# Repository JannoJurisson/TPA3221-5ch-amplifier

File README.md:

# TPA3221-5ch-amplifier
A D-class car amplifier based on TPA3221, replaces BOSE 294009 car amplifier PCB.

The amplifier uses a Push-pull SMPS with a SG3525 controller to boost 12V to 24V. Transformer is hand-made using non-gapped ferrite transformer core TDK E-50.
Similar E cores can be used as the transformer is fastened to the pcb using cable ties 

There a 5 channels:
Channel 1-4 -> speaker outputs (@ 4ohm speakers > ~4x60W)
Channel 5   -> subwoofer output (TPA3221 in PBTL operation, @ 4ohm woofer > ~100w)

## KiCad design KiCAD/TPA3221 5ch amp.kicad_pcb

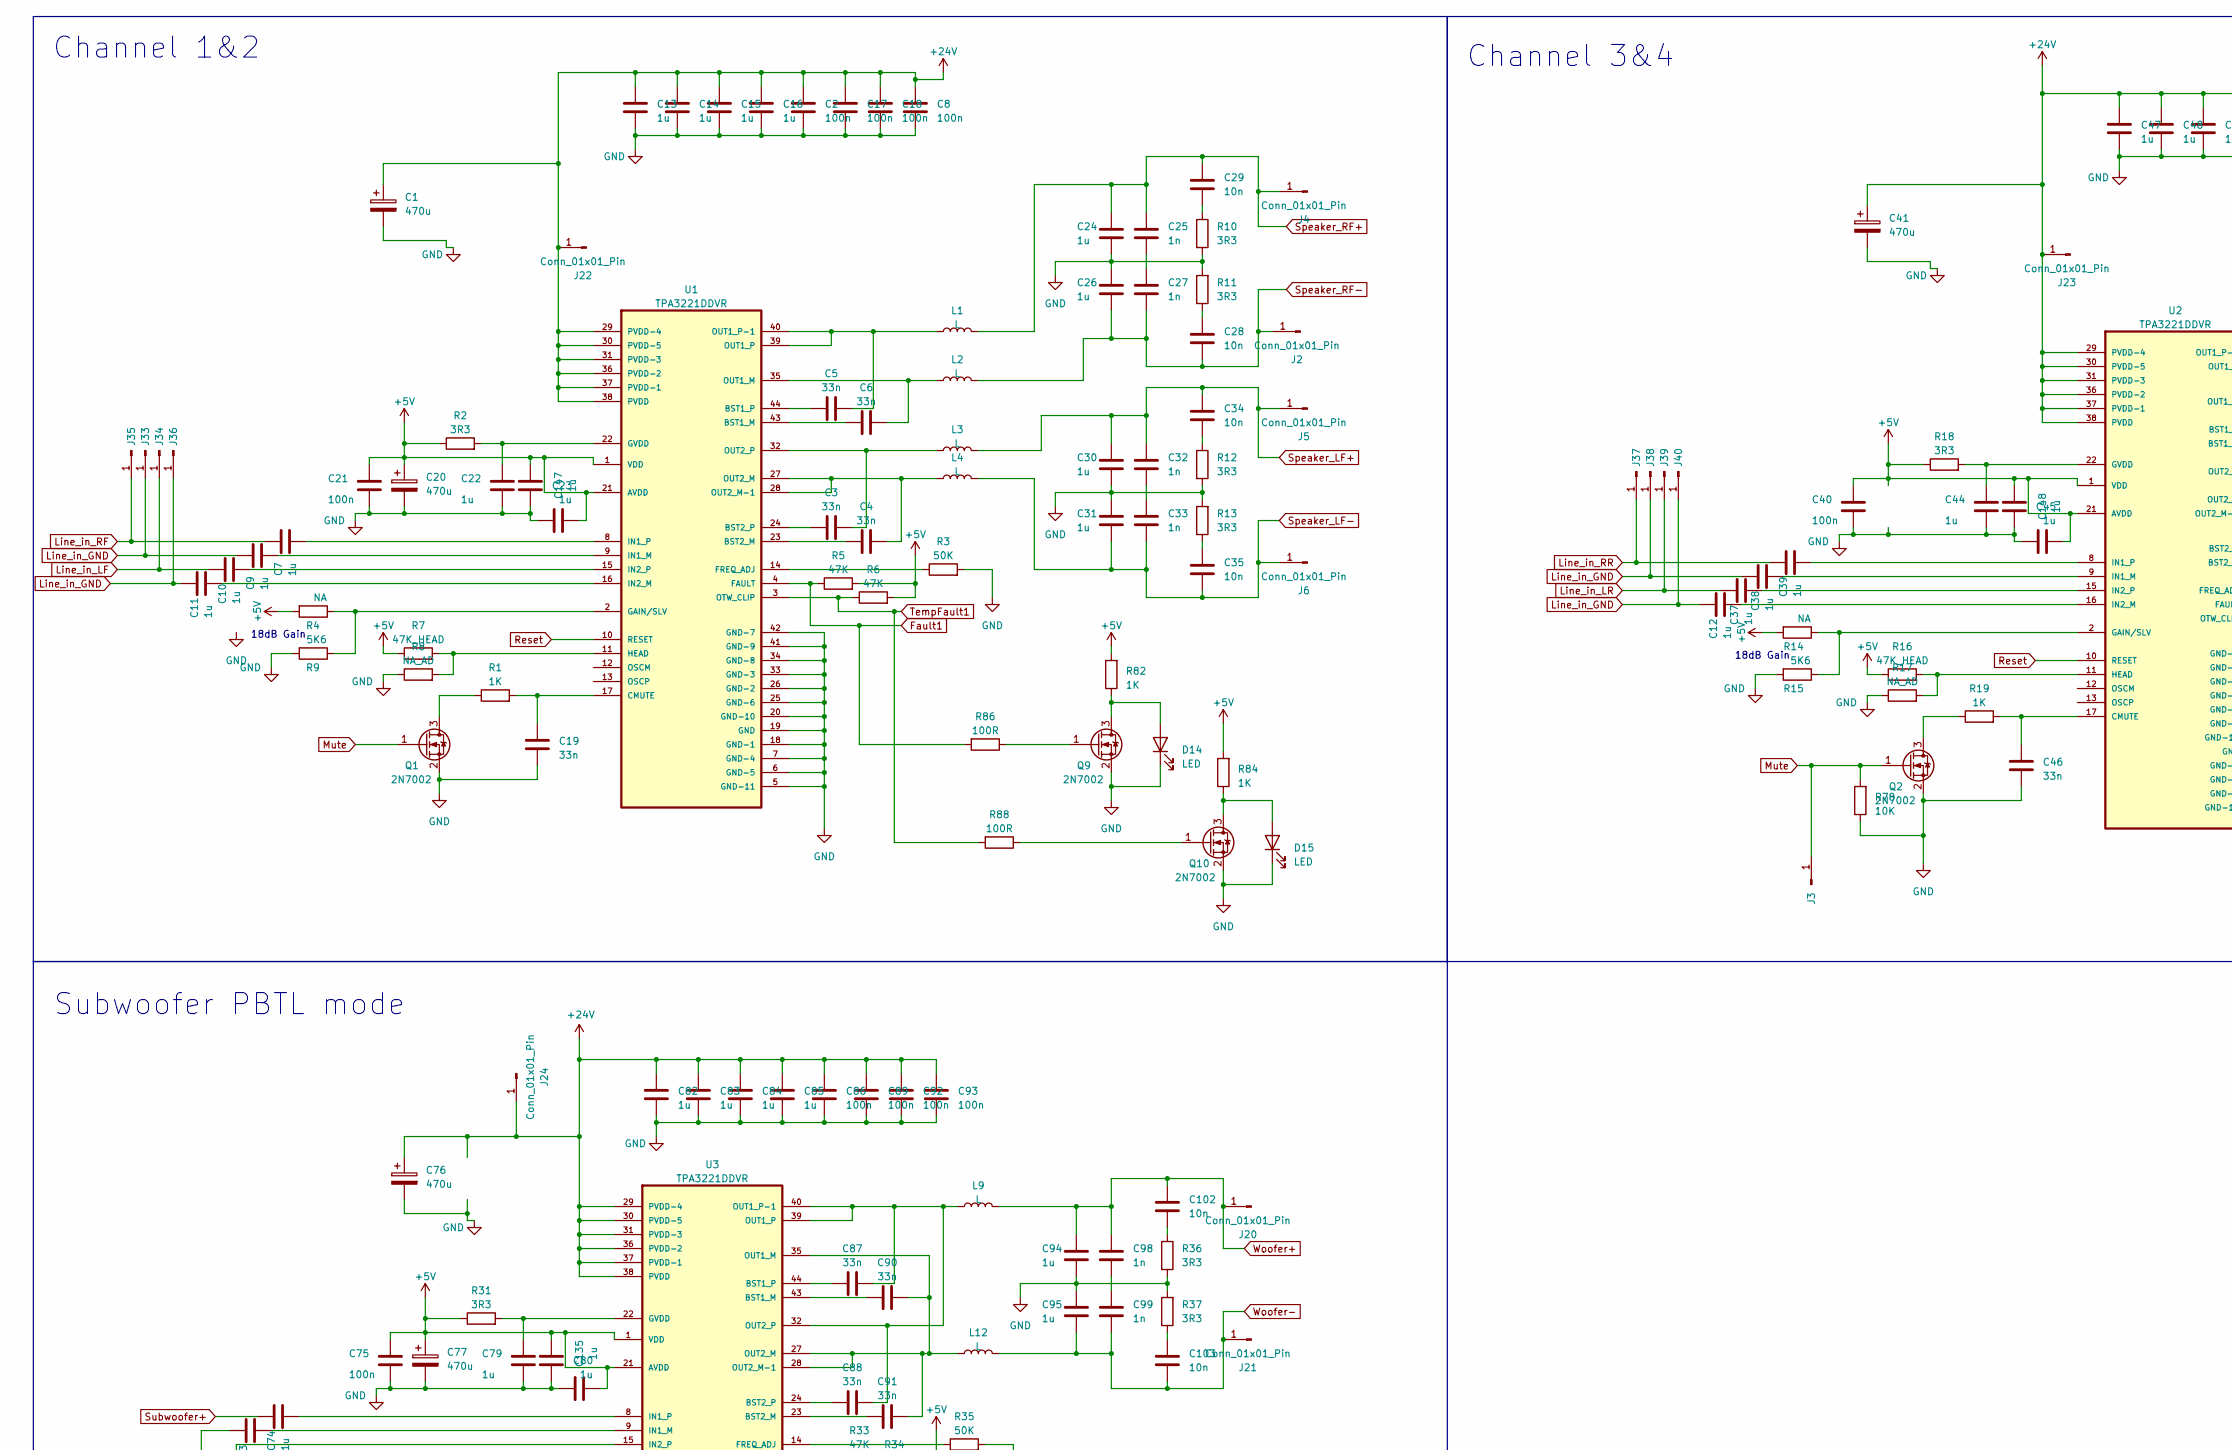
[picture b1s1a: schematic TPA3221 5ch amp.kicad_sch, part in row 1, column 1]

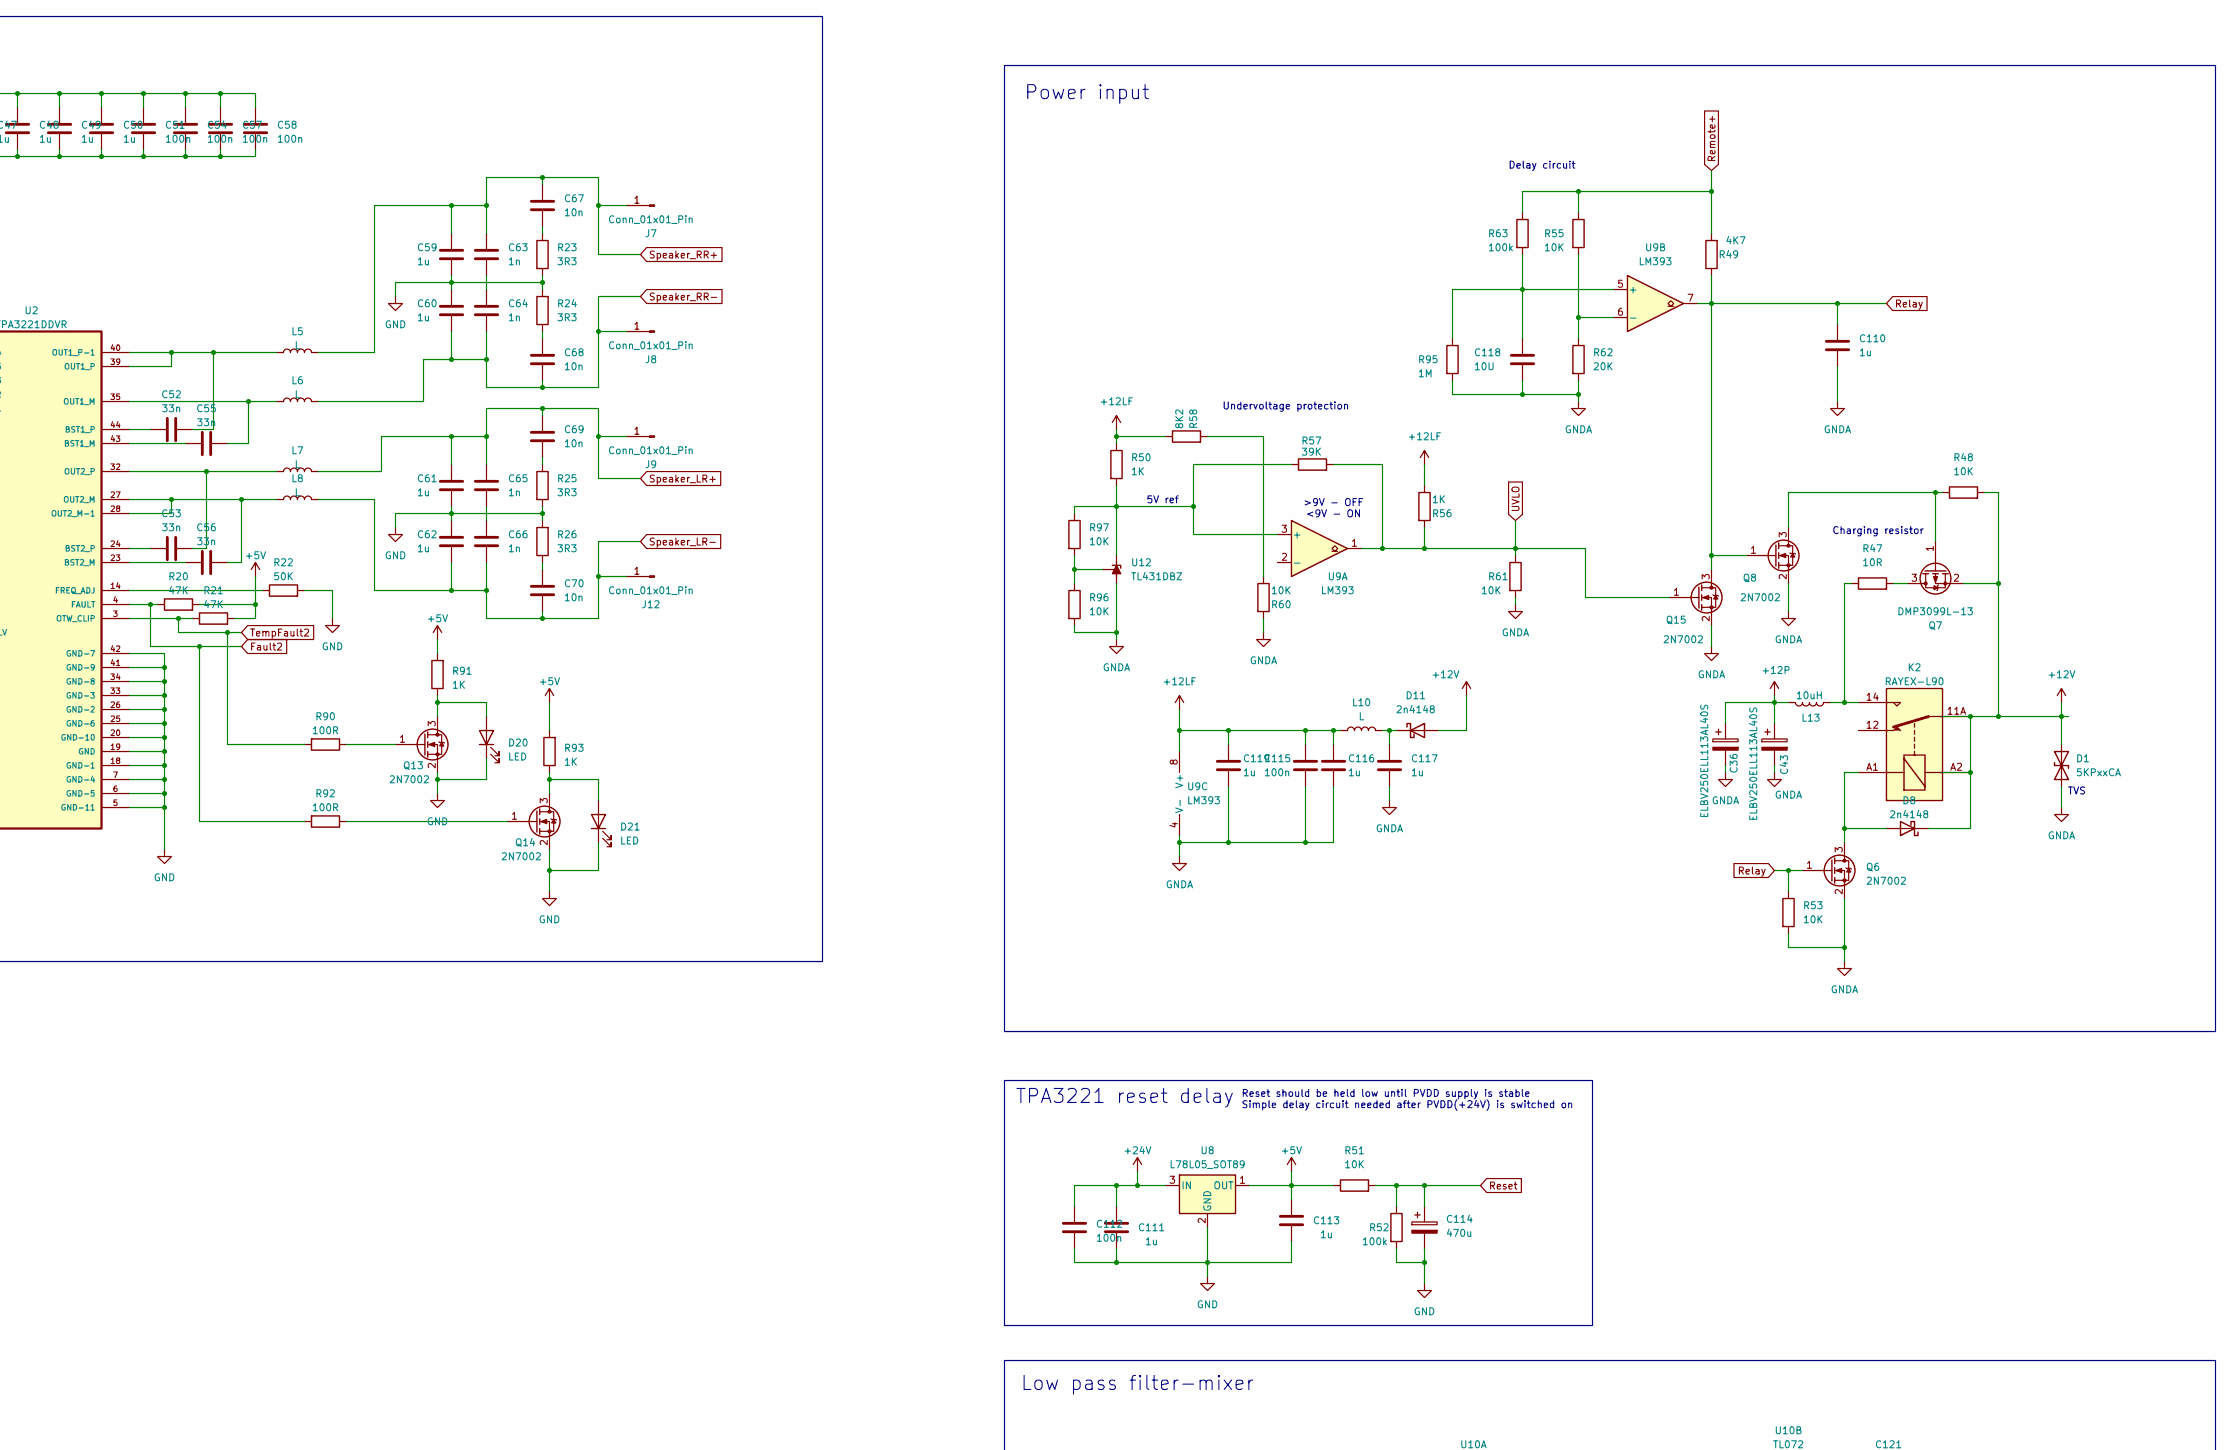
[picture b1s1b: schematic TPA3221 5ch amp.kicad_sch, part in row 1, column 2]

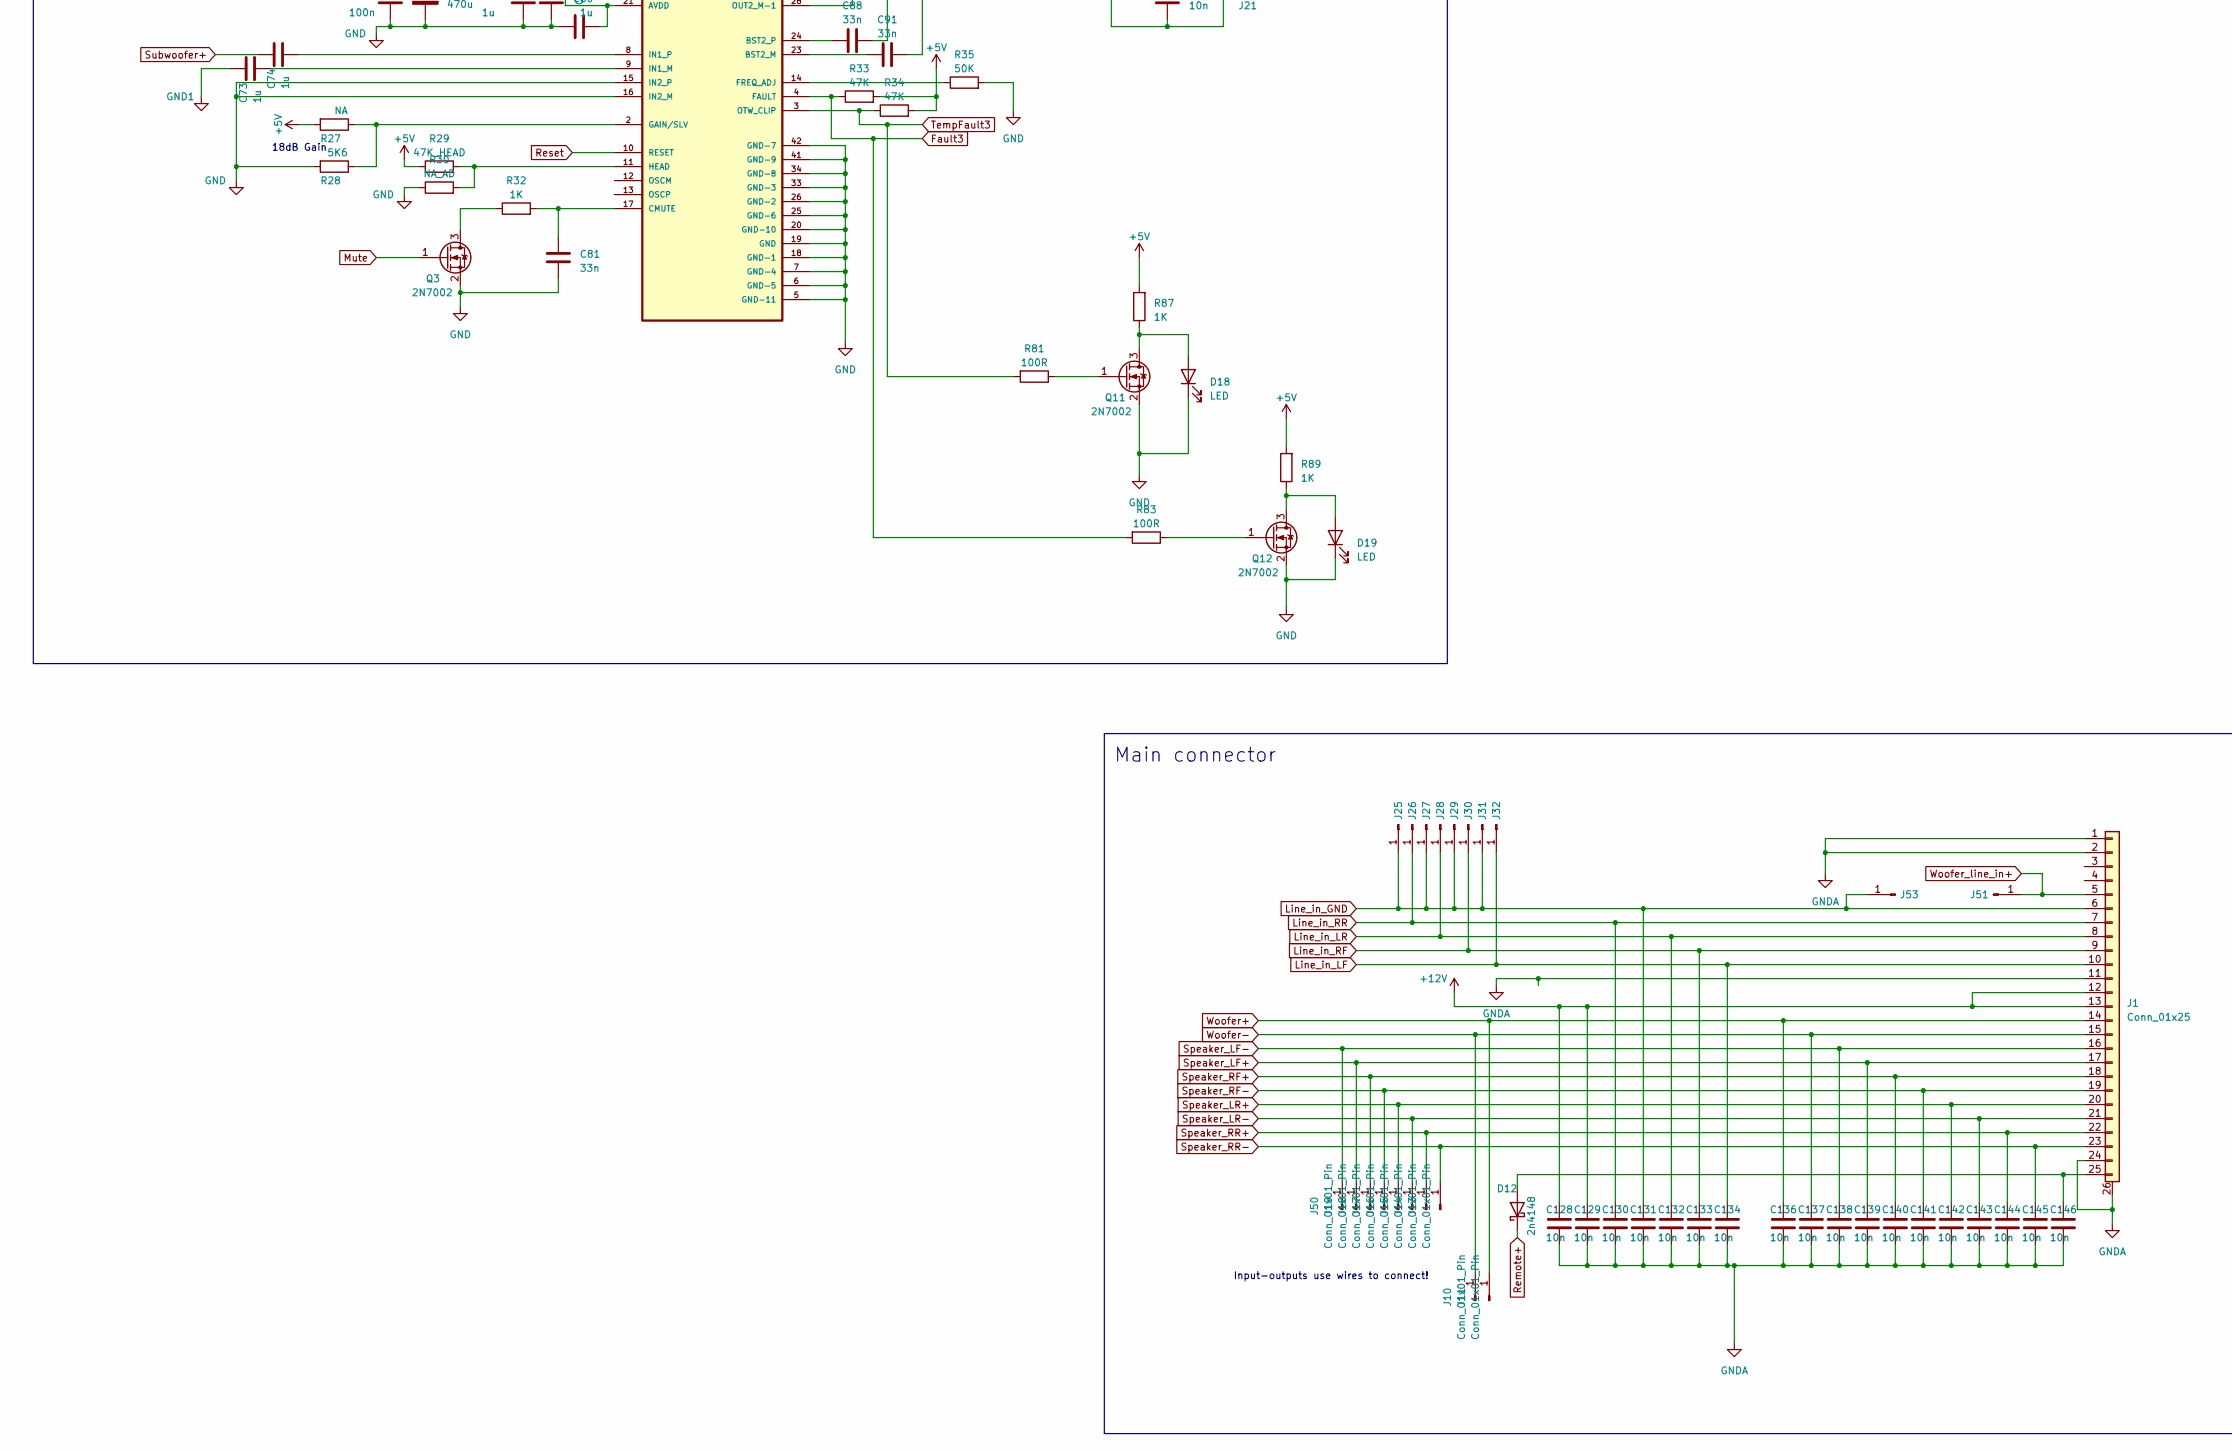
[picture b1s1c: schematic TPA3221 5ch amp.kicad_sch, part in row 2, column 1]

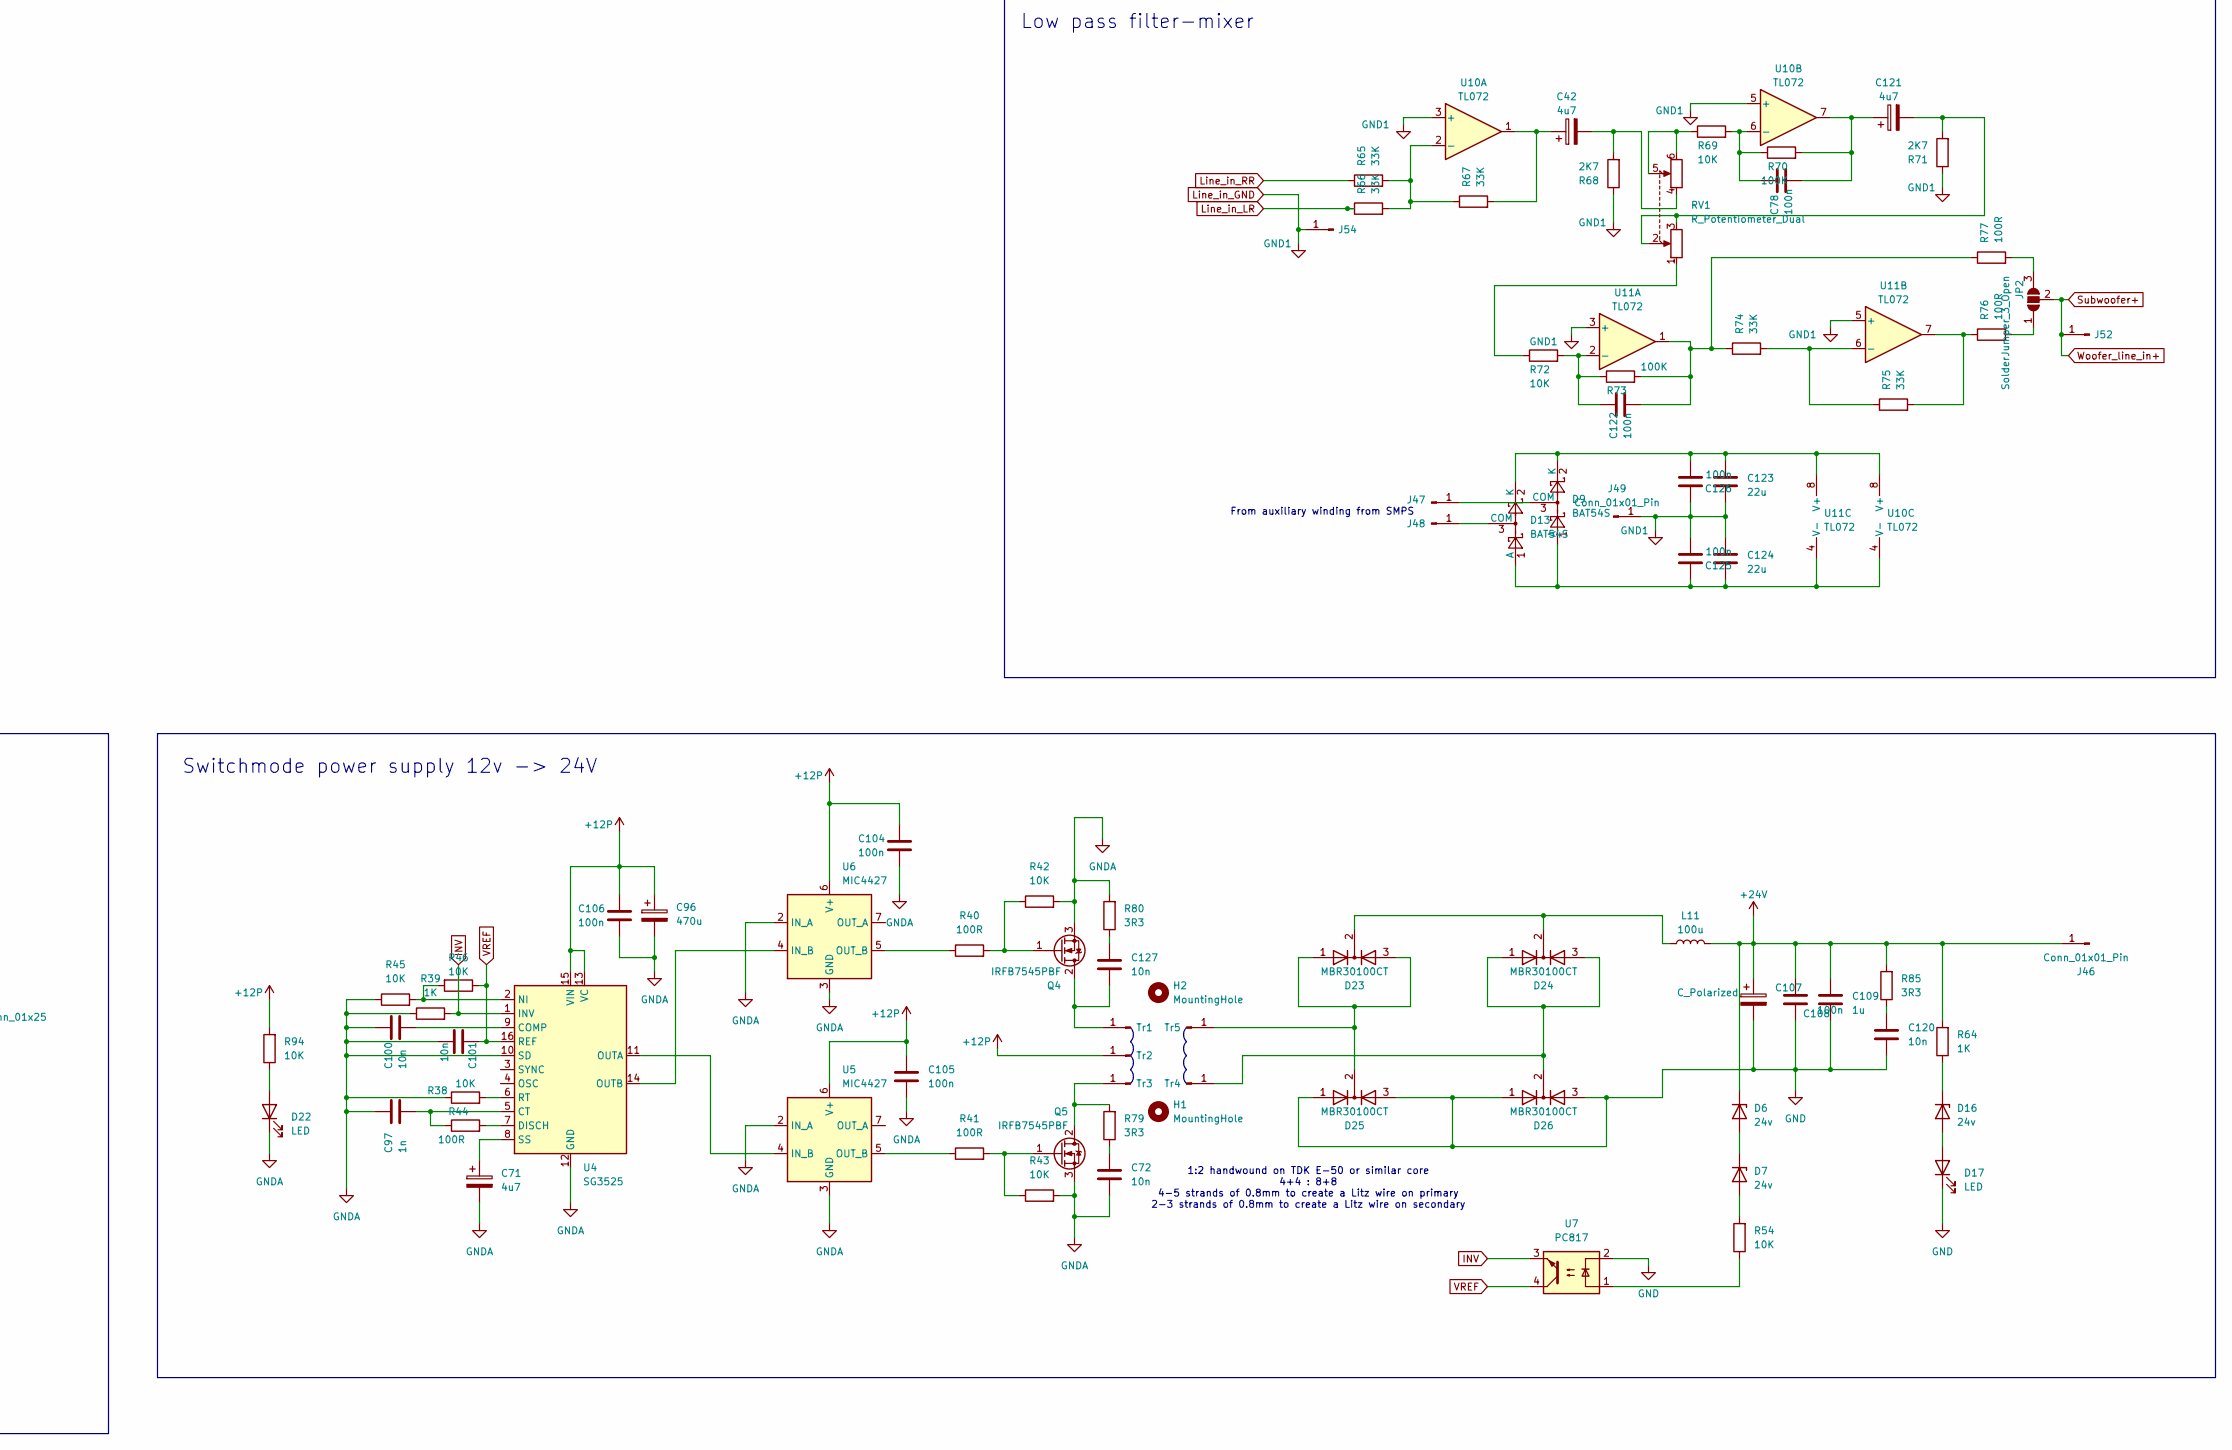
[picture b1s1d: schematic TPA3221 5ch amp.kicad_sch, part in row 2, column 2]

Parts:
C1, C41, C76: 470u; CP_Elec_10x12.5
C2, C8, C17, C18, C21, C40, C51, C54, C57, C58, C75, C86, C89, C92, C93, C104, C105, C106, C108, C112, C115, C125, C126: 100n; C_0603_1608Metric
C3, C4, C5, C6, C19, C46, C52, C53, C55, C56, C81, C87, C88, C90, C91: 33n; C_0603_1608Metric
C7, C9, C10, C11, C12, C24, C26, C30, C31, C37, C38, C39, C59, C60, C61, C62, C73, C74, C94, C95: 1u; C_Rect_L7.2mm_W4.5mm_P5.00mm_FKS2_FKP2_MKS2_MKP2
C13, C14, C15, C16, C47, C48, C49, C50, C82, C83, C84, C85, C109, C110, C111, C113, C116, C119: 1u; C_0805_2012Metric
C20: 470u; CP_Elec_6.3x5.4_Nichicon
C22, C23, C44, C45, C79, C80, C117, C135, C147, C148: 1u; C_0603_1608Metric
C25, C27, C32, C33, C63, C64, C65, C66, C97, C98, C99: 1n; C_0603_1608Metric
C28, C29, C34, C35, C67, C68, C69, C70, C100, C101, C102, C103: 10n; C_0603_1608Metric
C36, C43: ELBV250ELL113AL40S; CP_Radial_D18.0mm_P7.50mm
C42, C71, C121: 4u7; CP_Radial_D4.0mm_P2.00mm
C72, C120, C127, C128, C129, C130, C131, C132, C133, C134, C136, C137, C138, C139, C140, C141, C142, C143, C144, C145, C146: 10n; C_0805_2012Metric
C77: 470u; CP_Elec_6.3x5.2
C78, C122: 100n; C_Rect_L7.0mm_W3.5mm_P5.00mm
C96, C114: 470u; CP_Elec_6.3x5.4
C107: C_Polarized; CP_Radial_D18.0mm_P7.50mm
C118: 10U; C_0805_2012Metric
C123, C124: 22u; C_1206_3216Metric
D1: 5KPxxCA; D_P600_R-6_P20.00mm_Horizontal
D6, D7, D16: 24v; D_MiniMELF
D8, D11, D12: 2n4148; D_MiniMELF
D9, D13: BAT54S; SOT-23
D14, D15, D17, D18, D19, D20, D21, D22: LED; LED_0603_1608Metric
D23, D24, D25, D26: MBR30100CT; TO-220-3_Horizontal_TabDown
H1, H2: MountingHole; MountingHole_3.2mm_M3
J1: Conn_01x25; AMP_connector_Audi_AMP3510
J2, J4, J5, J6, J7, J8, J9, J10, J11, J12, J13, J14, J15, J16, J17, J18, J19, J20, J21, J22, J23, J24, J46, J50: Conn_01x01_Pin; SolderWire-1.5sqmm_1x01_D1.7mm_OD3mm
J3: MUTE; TestPoint_Keystone_5015_Micro-Minature
J25, J27, J29, J31, J33, J36, J38, J40, J53, J54: -; TestPoint_Keystone_5015_Micro-Minature
J26, J37: RR; TestPoint_Keystone_5015_Micro-Minature
J28, J39: LR; TestPoint_Keystone_5015_Micro-Minature
J30, J35: RF; TestPoint_Keystone_5015_Micro-Minature
J32, J34: LF; TestPoint_Keystone_5015_Micro-Minature
J41: Tr3; SolderWire-2.5sqmm_1x01_D2.4mm_OD4.4mm
J42: Tr2; SolderWire-2.5sqmm_1x01_D2.4mm_OD4.4mm
J43: Tr1; SolderWire-2.5sqmm_1x01_D2.4mm_OD4.4mm
J44: Tr5; SolderWire-2.5sqmm_1x01_D2.4mm_OD4.4mm
J45: Tr4; SolderWire-2.5sqmm_1x01_D2.4mm_OD4.4mm
J47, J48, J49: Conn_01x01_Pin; SolderWire-0.75sqmm_1x01_D1.25mm_OD2.3mm
J51: Woofer_in; TestPoint_Keystone_5015_Micro-Minature
J52: W_in; TestPoint_Keystone_5015_Micro-Minature
JP2: SolderJumper_3_Open; SolderJumper-3_P1.3mm_Open_RoundedPad1.0x1.5mm
K2: RAYEX-L90; Relay_SPDT_RAYEX-L90
L1, L2, L3, L4, L5, L6, L7, L8, L9, L12: L; L_Bourns_SRR1210A
L10: L; L_1210_3225Metric
L11: 100u; L_Radial_D16.8mm_P11.43mm_Vishay_IHB-1
L13: 10uH; L_Toroid_Horizontal_D32.5mm_P30.00mm_Bourns_2300
Q1, Q2, Q3, Q6, Q8, Q9, Q10, Q11, Q12, Q13, Q14, Q15: 2N7002; SOT-23
Q4, Q5: IRFB7545PBF; TO-220-3_Horizontal_TabDown
Q7: DMP3099L-13; SOT-23
R1, R19, R32, R39, R50, R56, R64, R82, R84, R87, R89, R91, R93: 1K; R_0603_1608Metric
R2, R10, R11, R12, R13, R18, R23, R24, R25, R26, R31, R36, R37, R79, R80, R85: 3R3; R_0805_2012Metric
R3, R22, R35: 50K; R_0805_2012Metric
R4, R14, R27: NA; R_0805_2012Metric
R5, R6, R20, R21, R33, R34: 47K; R_0603_1608Metric
R7, R16, R29: 47K_HEAD; R_0603_1608Metric
R8, R17, R30: NA_AD; R_0603_1608Metric
R9, R15, R28: 5K6; R_0805_2012Metric
R38, R42, R43, R45, R46, R48, R51, R53, R54, R55, R60, R61, R69, R72, R78, R94, R96, R97: 10K; R_0603_1608Metric
R40, R41: 100R; R_0805_2012Metric
R44, R76, R77, R81, R83, R86, R88, R90, R92: 100R; R_0603_1608Metric
R47: 10R; R_1210_3225Metric
R49: 4K7; R_0603_1608Metric
R52, R63: 100k; R_0603_1608Metric
R57: 39K; R_0603_1608Metric
R58: 8K2; R_0603_1608Metric
R62: 20K; R_0603_1608Metric
R65, R66, R67, R74, R75: 33K; R_0603_1608Metric
R68, R71: 2K7; R_0603_1608Metric
R70, R73: 100K; R_0603_1608Metric
R95: 1M; R_0603_1608Metric
RV1: R_Potentiometer_Dual; Potentiometer_Alpha_RD902F-40-00D_Dual_Vertical_CircularHol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
U1, U2, U3: TPA3221DDVR; SOP63P810X120-44N
U4: SG3525; SOIC-16_3.9x9.9mm_P1.27mm
U5, U6: MIC4427; SOIC-8_3.9x4.9mm_P1.27mm
U7: PC817; DIP-4_W7.62mm
U8: L78L05_SOT89; SOT-89-3
U9: LM393; SOIC-8_3.9x4.9mm_P1.27mm
U10, U11: TL072; SOIC-8_3.9x4.9mm_P1.27mm
U12: TL431DBZ; SOT-23

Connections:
+5V: C20.1, C21.1, C23.1, C40.1, C45.1, C75.1, C77.1, C80.1, C113.1, C135.2, C147.2, C148.2, R2.1, R4.2, R5.2, R6.2, R7.1, R14.2, R16.1, R18.1, R20.2, R21.2, R27.2, R29.1, R31.1, R33.2, R34.2, R51.1, R82.2, R84.2, R87.2, R89.2, R91.2, R93.2, U1.1 (VDD), U1.21 (AVDD), U2.1 (VDD), U2.21 (AVDD), U3.1 (VDD), U3.21 (AVDD), U8.1 (OUT)
+12LF: C115.1, C116.1, C119.1, L10.1, R50.1, R56.1, R58.1, U9.8 (V+)
+12P: C36.1, C43.1, C96.1, C104.1, C105.1, C106.1, J42.1, L13.2, R94.2, U4.13 (VC), U4.15 (VIN), U5.6 (V+), U6.6 (V+)
+12V: C128.2, C129.2, D1.1 (A1), D8.1 (K), D11.2 (A), J1.12, J1.13, K2.11A, K2.11B, K2.A2, Q7.2 (S), R48.2
+24V: C1.1, C2.1, C8.1, C13.1, C14.1, C15.1, C16.1, C17.1, C18.1, C41.1, C47.1, C48.1, C49.1, C50.1, C51.1, C54.1, C57.1, C58.1, C76.1, C82.1, C83.1, C84.1, C85.1, C86.1, C89.1, C92.1, C93.1, C107.1, C108.1, C109.1, C111.1, C112.1, D6.1 (K), J22.1, J23.1, J24.1, J46.1, L11.2, R64.2, R85.2, U1.29 (PVDD-4), U1.30 (PVDD-5), U1.31 (PVDD-3), U1.36 (PVDD-2), U1.37 (PVDD-1), U1.38 (PVDD), U2.29 (PVDD-4), U2.30 (PVDD-5), U2.31 (PVDD-3), U2.36 (PVDD-2), U2.37 (PVDD-1), U2.38 (PVDD), U3.29 (PVDD-4), U3.30 (PVDD-5), U3.31 (PVDD-3), U3.36 (PVDD-2), U3.37 (PVDD-1), U3.38 (PVDD), U8.3 (IN)
Fault1: R5.1, R86.2, U1.4 (FAULT)
Fault2: R20.1, R92.2, U2.4 (FAULT)
Fault3: R33.1, R83.2, U3.4 (FAULT)
GND: C1.2, C2.2, C8.2, C13.2, C14.2, C15.2, C16.2, C17.2, C18.2, C19.1, C20.2, C21.2, C22.2, C23.2, C24.1, C26.2, C30.1, C31.2, C40.2, C41.2, C44.2, C45.2, C46.1, C47.2, C48.2, C49.2, C50.2, C51.2, C54.2, C57.2, C58.2, C59.1, C60.2, C61.1, C62.2, C75.2, C76.2, C77.2, C79.2, C80.2, C81.1, C82.2, C83.2, C84.2, C85.2, C86.2, C89.2, C92.2, C93.2, C94.1, C95.2, C107.2, C108.2, C109.2, C111.2, C112.2, C113.2, C114.2, C120.1, C135.1, C147.1, C148.1, D14.1 (K), D15.1 (K), D17.1 (K), D18.1 (K), D19.1 (K), D20.1 (K), D21.1 (K), D25.1 (A), D25.3 (A), D26.1 (A), D26.3 (A), Q1.2 (S), Q2.2 (S), Q3.2 (S), Q9.2 (S), Q10.2 (S), Q11.2 (S), Q12.2 (S), Q13.2 (S), Q14.2 (S), R3.2, R8.1, R9.2, R10.2, R11.2, R12.2, R13.2, R15.2, R17.1, R22.2, R23.2, R24.2, R25.2, R26.2, R28.2, R30.1, R35.2, R36.2, R37.2, R52.2, R78.1, U1.5 (GND-11), U1.6 (GND-5), U1.7 (GND-4), U1.18 (GND-1), U1.19 (GND), U1.20 (GND-10), U1.25 (GND-6), U1.26 (GND-2), U1.33 (GND-3), U1.34 (GND-8), U1.41 (GND-9), U1.42 (GND-7), U2.5 (GND-11), U2.6 (GND-5), U2.7 (GND-4), U2.18 (GND-1), U2.19 (GND), U2.20 (GND-10), U2.25 (GND-6), U2.26 (GND-2), U2.33 (GND-3), U2.34 (GND-8), U2.41 (GND-9), U2.42 (GND-7), U3.5 (GND-11), U3.6 (GND-5), U3.7 (GND-4), U3.15 (IN2_P), U3.16 (IN2_M), U3.18 (GND-1), U3.19 (GND), U3.20 (GND-10), U3.25 (GND-6), U3.26 (GND-2), U3.33 (GND-3), U3.34 (GND-8), U3.41 (GND-9), U3.42 (GND-7), U7.2, U8.2 (GND)
GNDA: C36.2, C43.2, C71.2, C72.1, C96.2, C97.1, C100.1, C101.1, C104.2, C105.2, C106.2, C110.2, C115.2, C116.2, C117.2, C118.2, C119.2, C128.1, C129.1, C130.1, C131.1, C132.1, C133.1, C134.1, C136.1, C137.1, C138.1, C139.1, C140.1, C141.1, C142.1, C143.1, C144.1, C145.1, C146.1, D1.2 (A2), D22.1 (K), J1.1, J1.2, J1.11, J1.24, J1.26 (gnd), Q4.3 (S), Q5.3 (S), Q6.2 (S), Q8.2 (S), Q15.2 (S), R38.1, R39.1, R42.2, R43.2, R45.1, R53.2, R60.2, R61.2, R62.2, R80.2, R95.2, R96.2, U4.10 (SD), U4.12 (GND), U5.2 (IN_A), U5.3 (GND), U6.2 (IN_A), U6.3 (GND), U9.4 (V-), U12.3 (A)
INV: R39.2, U4.1 (INV), U7.3
Line_in_GND: C9.2, C11.2, C12.2, C38.2, C73.2, C123.2, C124.1, C125.2, C126.1, C131.2, J1.6, J25.1, J27.1, J29.1, J31.1, J33.1, J36.1, J38.1, J40.1, J49.1, J53.1, J54.1, R68.1, R71.1, U10.3 (+), U10.5 (+), U11.3 (+), U11.5 (+)
Line_in_LF: C10.2, C134.2, J1.10, J32.1, J34.1
Line_in_LR: C37.2, C132.2, J1.8, J28.1, J39.1, R66.1
Line_in_RF: C7.2, C133.2, J1.9, J30.1, J35.1
Line_in_RR: C39.2, C130.2, J1.7, J26.1, J37.1, R65.1
Mute: J3.1, Q1.1 (G), Q2.1 (G), Q3.1 (G), R78.2
unnamed: C25.1, C27.2
unnamed: C28.2, R11.1
unnamed: C29.1, R10.1
unnamed: C32.1, C33.2
unnamed: C34.1, R12.1
unnamed: C35.2, R13.1
unnamed: C42.1, R67.2, U10.1
unnamed: C42.2, R68.2, RV1.4
unnamed: C63.1, C64.2
unnamed: C65.1, C66.2
unnamed: C67.1, R23.1
unnamed: C68.2, R24.1
unnamed: C69.1, R25.1
unnamed: C70.2, R26.1
unnamed: C72.2, R79.1
unnamed: C98.1, C99.2
unnamed: C102.1, R36.1
unnamed: C103.2, R37.1
unnamed: C120.2, R85.1
unnamed: C78.1, C121.1, R70.2, U10.7
unnamed: C121.2, R71.2, RV1.2, RV1.3
unnamed: C122.1, R73.2, R74.1, R77.1, U11.1
unnamed: C127.2, R80.1
unnamed: D6.2 (A), D7.1 (K)
unnamed: D7.2 (A), R54.2
unnamed: D8.2 (A), K2.A1, Q6.3 (D)
unnamed: D9.3 (COM), J47.1
unnamed: C117.1, D11.1 (K), L10.2
unnamed: C146.2, D12.2 (A), J1.25
unnamed: C124.2, C125.1, D9.1 (A), D13.1 (A), U10.4 (V-), U11.4 (V-)
unnamed: D13.3 (COM), J48.1
unnamed: C123.1, C126.2, D9.2 (K), D13.2 (K), U10.8 (V+), U11.8 (V+)
unnamed: D14.2 (A), Q9.3 (D), R82.1
unnamed: D15.2 (A), Q10.3 (D), R84.1
unnamed: D16.2 (A), D17.2 (A)
unnamed: D16.1 (K), R64.1
unnamed: D18.2 (A), Q11.3 (D), R87.1
unnamed: D19.2 (A), Q12.3 (D), R89.1
unnamed: D20.2 (A), Q13.3 (D), R91.1
unnamed: D21.2 (A), Q14.3 (D), R93.1
unnamed: D22.2 (A), R94.1
unnamed: D23.2 (K), D24.2 (K), L11.1
unnamed: D23.1 (A), D23.3 (A), D25.2 (K), J44.1
unnamed: D24.1 (A), D24.3 (A), D26.2 (K), J45.1
unnamed: J41.1, Q5.2 (D), R79.2
unnamed: C127.1, J43.1, Q4.2 (D)
unnamed: JP2.1 (A), R76.2
unnamed: JP2.3 (B), R77.2
unnamed: K2.14, L13.1, R47.1
unnamed: Q1.3 (D), R1.1
unnamed: Q2.3 (D), R19.1
unnamed: Q3.3 (D), R32.1
unnamed: Q4.1 (G), R40.2, R42.1
unnamed: Q5.1 (G), R41.2, R43.1
unnamed: Q7.3 (D), R47.2
unnamed: Q7.1 (G), Q8.3 (D), R48.1
unnamed: Q9.1 (G), R86.1
unnamed: Q10.1 (G), R88.1
unnamed: Q11.1 (G), R81.1
unnamed: Q12.1 (G), R83.1
unnamed: Q13.1 (G), R90.1
unnamed: Q14.1 (G), R92.1
unnamed: R54.1, U7.1
unnamed: R58.2, R60.1
unnamed: R69.1, RV1.5, RV1.6
unnamed: R72.1, RV1.1
unnamed: R75.2, R76.1, U11.7
unnamed: C6.1, U1.43 (BST1_M)
unnamed: C5.1, U1.44 (BST1_P)
unnamed: C4.1, U1.23 (BST2_M)
unnamed: C3.1, U1.24 (BST2_P)
unnamed: C19.2, R1.2, U1.17 (CMUTE)
unnamed: R3.1, U1.14 (FREQ_ADJ)
unnamed: R4.1, R9.1, U1.2 (GAIN/SLV)
unnamed: C22.1, R2.2, U1.22 (GVDD)
unnamed: R7.2, R8.2, U1.11 (HEAD)
unnamed: C9.1, U1.9 (IN1_M)
unnamed: C7.1, U1.8 (IN1_P)
unnamed: C11.1, U1.16 (IN2_M)
unnamed: C10.1, U1.15 (IN2_P)
unnamed: C6.2, L2.1, U1.35 (OUT1_M)
unnamed: C5.2, L1.1, U1.39 (OUT1_P), U1.40 (OUT1_P-1)
unnamed: C4.2, L4.1, U1.27 (OUT2_M), U1.28 (OUT2_M-1)
unnamed: C3.2, L3.1, U1.32 (OUT2_P)
unnamed: C55.1, U2.43 (BST1_M)
unnamed: C52.1, U2.44 (BST1_P)
unnamed: C56.1, U2.23 (BST2_M)
unnamed: C53.1, U2.24 (BST2_P)
unnamed: C46.2, R19.2, U2.17 (CMUTE)
unnamed: R22.1, U2.14 (FREQ_ADJ)
unnamed: R14.1, R15.1, U2.2 (GAIN/SLV)
unnamed: C44.1, R18.2, U2.22 (GVDD)
unnamed: R16.2, R17.2, U2.11 (HEAD)
unnamed: C38.1, U2.9 (IN1_M)
unnamed: C39.1, U2.8 (IN1_P)
unnamed: C12.1, U2.16 (IN2_M)
unnamed: C37.1, U2.15 (IN2_P)
unnamed: C55.2, L6.1, U2.35 (OUT1_M)
unnamed: C52.2, L5.1, U2.39 (OUT1_P), U2.40 (OUT1_P-1)
unnamed: C56.2, L8.1, U2.27 (OUT2_M), U2.28 (OUT2_M-1)
unnamed: C53.2, L7.1, U2.32 (OUT2_P)
unnamed: C90.1, U3.43 (BST1_M)
unnamed: C87.1, U3.44 (BST1_P)
unnamed: C91.1, U3.23 (BST2_M)
unnamed: C88.1, U3.24 (BST2_P)
unnamed: C81.2, R32.2, U3.17 (CMUTE)
unnamed: R35.1, U3.14 (FREQ_ADJ)
unnamed: R27.1, R28.1, U3.2 (GAIN/SLV)
unnamed: C79.1, R31.2, U3.22 (GVDD)
unnamed: R29.2, R30.2, U3.11 (HEAD)
unnamed: C73.1, U3.9 (IN1_M)
unnamed: C74.1, U3.8 (IN1_P)
unnamed: C90.2, C91.2, L12.1, U3.27 (OUT2_M), U3.28 (OUT2_M-1), U3.35 (OUT1_M)
unnamed: C87.2, C88.2, L9.1, U3.32 (OUT2_P), U3.39 (OUT1_P), U3.40 (OUT1_P-1)
unnamed: C100.2, U4.9 (COMP)
unnamed: C97.2, R44.1, U4.5 (CT)
unnamed: R44.2, U4.7 (DISCH)
unnamed: R45.2, R46.2, U4.2 (NI)
unnamed: U4.11 (OUTA), U5.4 (IN_B)
unnamed: U4.14 (OUTB), U6.4 (IN_B)
unnamed: R38.2, U4.6 (RT)
unnamed: C71.1, U4.8 (SS)
unnamed: R41.1, U5.5 (OUT_B)
unnamed: R40.1, U6.5 (OUT_B)
unnamed: C118.1, R63.2, R95.1, U9.5 (+)
unnamed: R55.2, R62.1, U9.6 (-)
unnamed: R65.2, R66.2, R67.1, U10.2 (-)
unnamed: C78.2, R69.2, R70.1, U10.6 (-)
unnamed: C122.2, R72.2, R73.1, U11.2 (-)
unnamed: R74.2, R75.1, U11.6 (-)
unnamed: R50.2, R57.1, R97.1, U9.3 (+), U12.1 (K)
unnamed: R96.1, R97.2, U12.2 (REF)
Relay: C110.1, Q6.1 (G), Q8.1 (G), Q15.3 (D), R49.1, R53.1, U9.7
Remote+: D12.1 (K), R49.2, R55.1, R63.1
Reset: C114.1, R51.2, R52.1, U1.10 (RESET), U2.10 (RESET), U3.10 (RESET)
Speaker_LF+: C30.2, C32.2, C34.2, C139.2, J1.17, J5.1, J19.1, L3.2
Speaker_LF-: C31.1, C33.1, C35.1, C138.2, J1.16, J6.1, J50.1, L4.2
Speaker_LR+: C61.2, C65.2, C69.2, C142.2, J1.20, J9.1, J16.1, L7.2
Speaker_LR-: C62.1, C66.1, C70.1, C143.2, J1.21, J12.1, J15.1, L8.2
Speaker_RF+: C24.2, C25.2, C29.2, C140.2, J1.18, J4.1, J18.1, L1.2
Speaker_RF-: C26.1, C27.1, C28.1, C141.2, J1.19, J2.1, J17.1, L2.2
Speaker_RR+: C59.2, C63.2, C67.2, C144.2, J1.22, J7.1, J14.1, L5.2
Speaker_RR-: C60.1, C64.1, C68.1, C145.2, J1.23, J8.1, J13.1, L6.2
Subwoofer+: C74.2, J1.5, J51.1, J52.1, JP2.2 (C)
TempFault1: R6.1, R88.2, U1.3 (OTW_CLIP)
TempFault2: R21.1, R90.2, U2.3 (OTW_CLIP)
TempFault3: R34.1, R81.2, U3.3 (OTW_CLIP)
UVLO: Q15.1 (G), R56.2, R57.2, R61.1, U9.1
VREF: C101.2, R46.1, U4.16 (REF), U7.4
Woofer+: C94.2, C98.2, C102.2, C136.2, J1.14, J11.1, J20.1, L9.2
Woofer-: C95.1, C99.1, C103.1, C137.2, J1.15, J10.1, J21.1, L12.2

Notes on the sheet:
TVS
Undervoltage protection
Charging resistor
Channel 1&2
5V ref
Switchmode power supply 12v -> 24V
Input-outputs use wires to connect!
Low pass filter-mixer
18dB Gain
>9V - OFF <9V - ON
TPA3221 reset delay
Subwoofer PBTL mode
Delay circuit
Reset should be held low until PVDD supply is stable Simple delay circuit needed after PVDD(+24V) is switched on
Power input
Main connector
From auxiliary winding from SMPS
Channel 3&4
1:2 handwound on TDK E-50 or similar core 4+4 : 8+8 4-5 strands of 0.8mm to create a Litz wire on primary 2-3 strands of 0.8mm to create a Litz wire on secondary

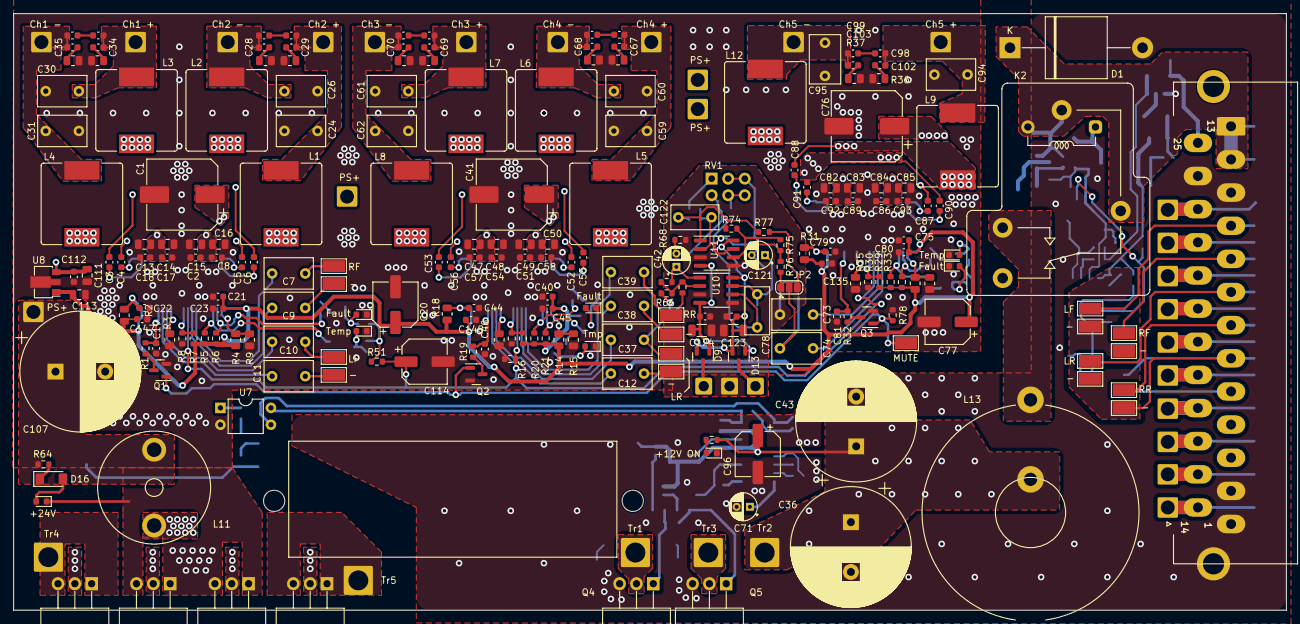
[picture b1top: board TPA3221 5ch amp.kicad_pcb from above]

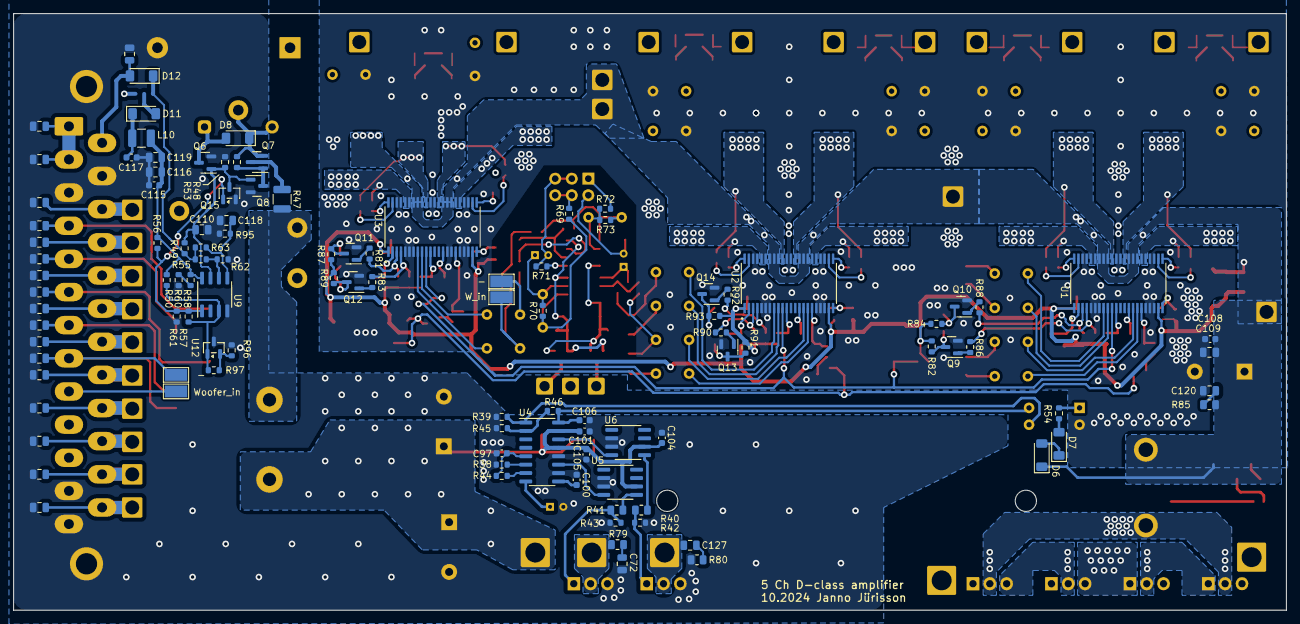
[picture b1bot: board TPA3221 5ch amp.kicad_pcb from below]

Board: 2 copper layers, 192.0 x 90.0 mm, 364 parts (109 on the bottom side), 168 nets.
